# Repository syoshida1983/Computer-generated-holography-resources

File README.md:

# Computer-generated holography resources

## CGH
C++ program for hologram calculation. [Visual Studio](https://visualstudio.microsoft.com/downloads/) is required to build the program.

### Build and Run
[Wave Field Library (WFL)](http://www.laser.ee.kansai-u.ac.jp/WaveFieldTools/download/wfl.html) and [Polygon Source Library (PSL)](http://www.laser.ee.kansai-u.ac.jp/WaveFieldTools/download/psl.html) are required to build the program.
To build the program, download and install the above two libraries.
After installation, add the "include" directory in the library's installation path to the "[Additional Include Directories](https://learn.microsoft.com/en-us/cpp/build/reference/i-additional-include-directories)" of the Visual Studio project.
  Similarly, add "wfl3.lib" and "psl.lib" in the "lib" directory of the installation path to "[Additional Dependencies](https://learn.microsoft.com/en-us/cpp/build/reference/linker-property-pages#input-property-page)."

"wfl3.dll" and "psl.dll" are required to run the program.
These files are in the "bin" directory of the installation path.
[Intel Compilers Runtime Libraries](https://www.intel.com/content/www/us/en/developer/articles/tool/compilers-redistributable-libraries-by-version.html) are also required to run the program.

## Jig
Drawings of the jig used to secure the DMD evaluation board [DLPLCR6500EVM](https://www.ti.com/product/DLPLCR6500EVM/part-details/DLPLCR6500EVM) to the lab bench.
Files are provided in STEP format.

## LD-Driver
Circuit schematic and PCB layout of common anode 3-channel LD driver.
Files are provided in .sch and .brd format.
- For each LD, connect the anode to the power supply (+V) and the cathode to R-LD(K), G-LD(K), or B-LD(K).
- The current between +V and R-LD(K) is determined by the ratio of the input voltage to R-DRV and the resistor R2. Similarly, the currents of the other two channels are determined by G-DRV and R6 and B-DRV and R10.
- Connect variable resistors to R-VOL, G-VOL, and B-VOL to adjust the current.
- Use n-channel power MOSFETs for Q1, Q2, and Q3 and a quad operational amplifier with a typical pin assignment for the OPAMP.
- Molex connector 53047-0510 is for connection to HOLOEYE LETO-3.

## Citation
```BibTeX
@article{Yoshida2024,
	author		= {Shuhei Yoshida},
	doi		= {10.1364/AO.509556},
	issue		= {10},
	journal		= {Applied Optics},
	month		= {3},
	pages		= {2455-2461},
	publisher	= {Optica Publishing Group},
	title		= {High-speed full-color computer-generated holography using a digital micromirror device and fiber-coupled RGB laser diode},
	volume		= {63},
	url		= {https://opg.optica.org/ao/abstract.cfm?uri=ao-63-10-2455},
	year		= {2024},
}
```

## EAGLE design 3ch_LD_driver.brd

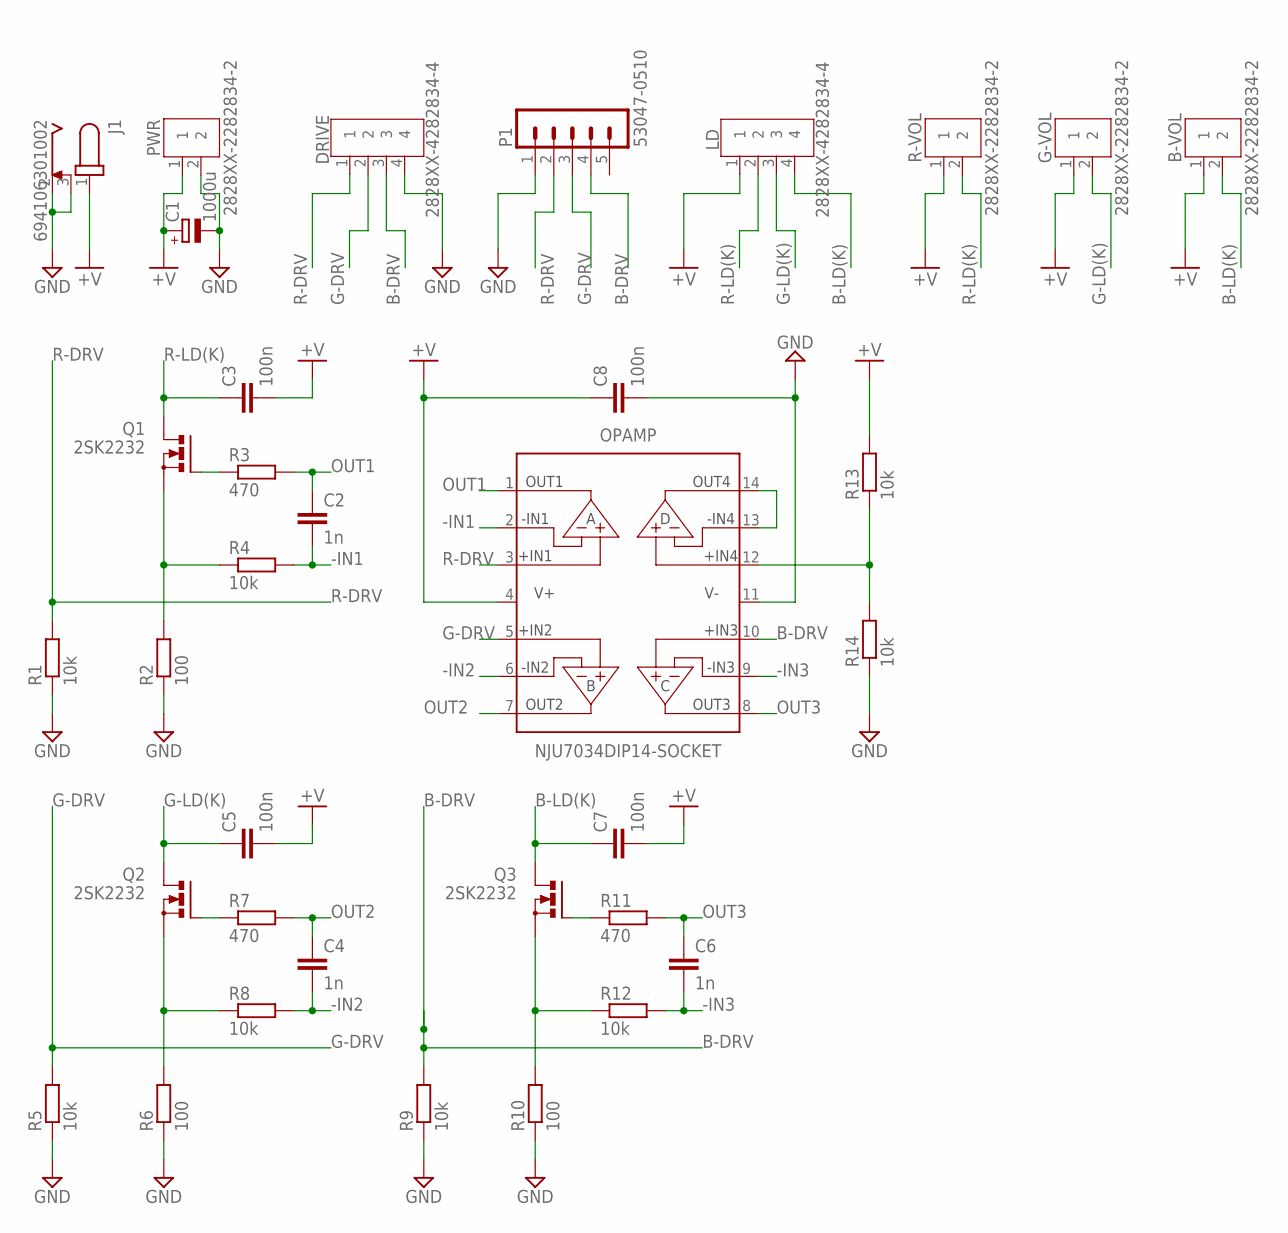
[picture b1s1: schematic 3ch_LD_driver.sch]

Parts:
B-VOL: 2828XX-2282834-2; TERMBLK_254-2N
C1: 1000u; E5-10,5
C2, C4, C6: 1n; C025-024X044
C3, C5, C7, C8: 100n; C025-024X044
DRIVE: 2828XX-4282834-4; TERMBLK_254-4N
G-VOL: 2828XX-2282834-2; TERMBLK_254-2N
J1: 694106301002
LD: 2828XX-4282834-4; TERMBLK_254-4N
OPAMP: NJU7034DIP14-SOCKET; DIP14-SOCKET
P1: 53047-0510
PWR: 2828XX-2282834-2; TERMBLK_254-2N
Q1, Q2, Q3: 2SK2232; TO220BV
R1, R4, R5, R8, R9, R12, R13, R14: 10k; 0207/10
R2, R6, R10: 100; 0207/10
R3, R7, R11: 470; 0207/10
R-VOL: 2828XX-2282834-2; TERMBLK_254-2N

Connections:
+V: B-VOL.1, C1.+, C3.2, C5.2, C7.2, C8.1, G-VOL.1, J1.1, LD.1, OPAMP.4 (V+), PWR.1, R13.2, R-VOL.1
-IN1: C2.2, OPAMP.2 (-IN1), R4.2
-IN2: C4.2, OPAMP.6 (-IN2), R8.2
-IN3: C6.2, OPAMP.9 (-IN3), R12.2
B-DRV: DRIVE.3, OPAMP.10 (+IN3), P1.4, R9.2
B-LD(K): B-VOL.2, C7.1, LD.4, Q3.D
G-DRV: DRIVE.2, OPAMP.5 (+IN2), P1.3, R5.2
G-LD(K): C5.1, G-VOL.2, LD.3, Q2.D
GND: C1.-, C8.2, DRIVE.4, J1.2, J1.3, OPAMP.11 (V-), P1.1, PWR.2, R1.1, R2.1, R5.1, R6.1, R9.1, R10.1, R14.1
unnamed: Q2.S, R6.2, R8.1
unnamed: Q1.G, R3.1
unnamed: Q1.S, R2.2, R4.1
unnamed: Q2.G, R7.1
unnamed: Q3.S, R10.2, R12.1
unnamed: Q3.G, R11.1
unnamed: OPAMP.13 (-IN4), OPAMP.14 (OUT4)
unnamed: OPAMP.12 (+IN4), R13.1, R14.2
OUT1: C2.1, OPAMP.1 (OUT1), R3.2
OUT2: C4.1, OPAMP.7 (OUT2), R7.2
OUT3: C6.1, OPAMP.8 (OUT3), R11.2
R-DRV: DRIVE.1, OPAMP.3 (+IN1), P1.2, R1.2
R-LD(K): C3.1, LD.2, Q1.D, R-VOL.2

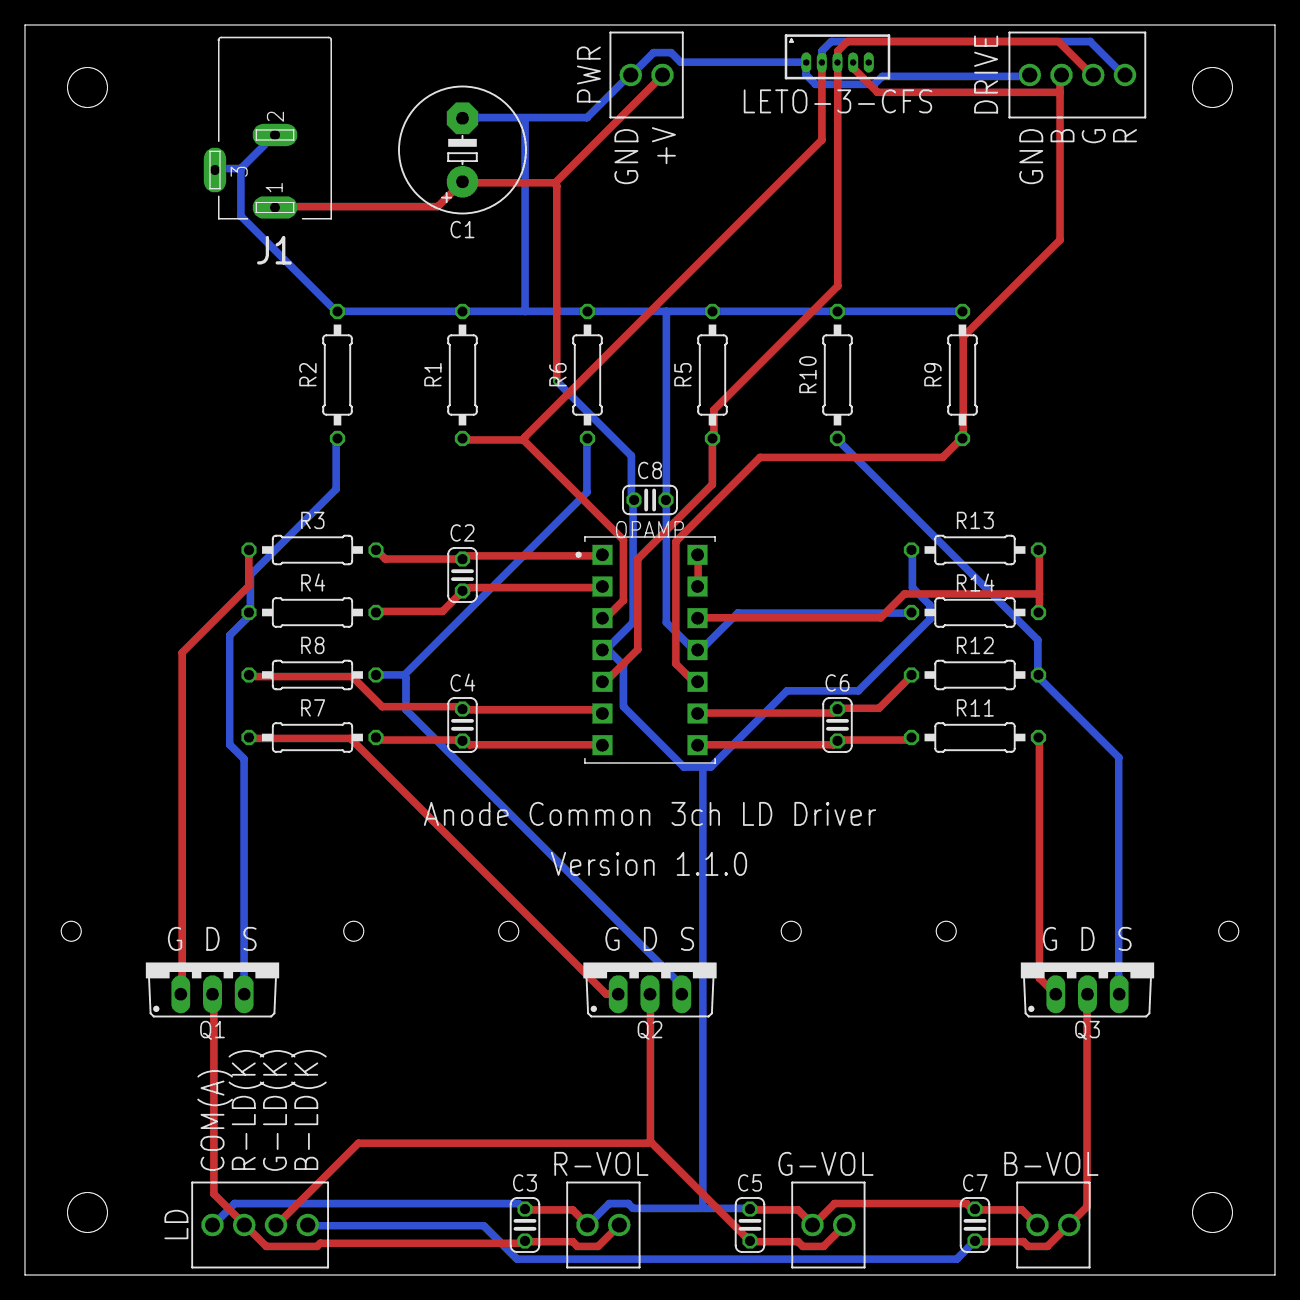
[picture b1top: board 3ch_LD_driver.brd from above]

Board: 2 copper layers, 100.0 x 100.0 mm, 34 parts (0 on the bottom side), 22 nets.

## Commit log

2023-08-18 Rename 3ch_LD_driver.brd to LD-driver/3ch_LD_driver.brd
2023-08-18 Rename 3ch_LD_driver.sch to LD-driver/3ch_LD_driver.sch
2024-02-13 Create LICENSE
